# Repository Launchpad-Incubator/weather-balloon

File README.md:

# Weather Balloon Research

This is the research repository for the Launchpad weather balloon project. Add any useful information in the [wiki](https://github.com/Launchpad-Incubator/weather-balloon/wiki) under the appropriate page.

## Project Links

N/A (for now - **put OnShape link here**!)

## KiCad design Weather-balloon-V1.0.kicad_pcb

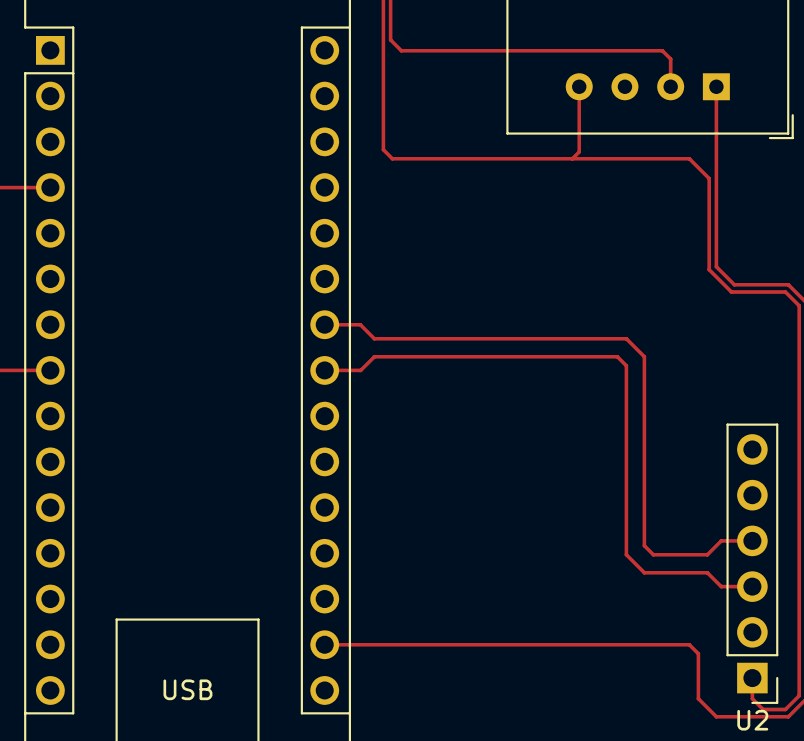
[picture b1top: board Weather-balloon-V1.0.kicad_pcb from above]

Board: 2 copper layers, 3 parts (0 on the bottom side), 5 nets.

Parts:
A1: Arduino_Nano_ESP32; Arduino_Nano
U1: AM2302; ASAIR_AM2302_P2.54mm_Vertical
U2: BMP280; PinHeader_1x06_P2.54mm_Vertical

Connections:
unnamed: A1.17 (3V3), U1.1 (VDD)
unnamed: A1.8 (D5), U1.2 (SDA)
unnamed: A1.4 (GND), A1.29 (GND), U1.3 (GND), U1.4 (GND), U2.1 (GND)
unnamed: A1.24 (SCL/A5), U2.4 (SCK)
unnamed: A1.23 (SDA/A4), U2.3 (SDI)

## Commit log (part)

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2025-10-22 Revise README for weather balloon project
    Updated project title and added description and links section.
2025-10-26 Update README with wiki link
2025-10-26 Add Project Links section to README
    Added a section for project links in the README.
2025-10-26 Add GitHub Actions for issue management automation
2025-10-26 Refactor issue management workflow conditions
2025-10-26 Add label-commenter configuration for duplicates
2025-10-26 Add permissions for issues in workflow
2025-10-26 Update README to highlight OnShape link placement
2025-10-26 Update project URL in GitHub Actions workflow
2025-10-29 Add contributing section to README
2025-11-08 Move README to .github directory
2025-11-09 Add Skew-T plot image
2025-11-09 Rename Screenshot 2025-10-26 155839.png to images/Skew-T_plot.png
2025-11-29 Add Spot Trace weight to component_weights.md
2026-01-22 Add Arduino Weather Station code
    Initial implementation of Arduino Weather Station code that reads temperature, humidity, and pressure from sensors and displays the data on a Nokia LCD.
2026-01-22 add correct file extension
2026-01-22 make compatible w/ Arduino Nano ESP32
2026-01-29 remove bmp085 calibration variables
2026-01-29 fix inverted logic D:
2026-01-29 cleaning up read sensors function and adding better logic :)
2026-01-29 fix the logic, fix dual variable assignment, and fix the structure being in inverse order
2026-01-29 add emoticons because i was bored and had nothing to do ¯\_(ツ)_/¯
2026-01-29 Rename code.ino to Code/archivedCode/code.ino
2026-01-29 Rename Code(BMP280Version).ino to main.ino
2026-02-05 Add enum, make cleaner logic, and QOL upd
2026-02-08 rename Images to Resources
2026-02-08 list the pins in the resources folder
2026-02-08 Update pinsForWiring
2026-02-08 <----- the pins for wiring are in here
2026-02-08 <----- code is in here
2026-02-12 <- Code w/ gps module
    Also has bmp 280 functionality & more
2026-02-12 fixed the gps thingy :D
2026-02-12 added the BMP280 without gps version here
2026-02-19 fix code
2026-02-19 Add APRS Notes for balloon tracking
    Added detailed notes for APRS balloon tracking including header format and data interpretation.
2026-02-19 <-- wiring here
2026-02-19 Revise timestamp format and add new APRS data
    Updated APRS Notes with corrected timestamp format and additional data.
2026-02-19 <-- things for payload that are important
2026-02-25 The code is in weather-balloon/Code/archivedCode/mainCode.ino
2026-02-26 <-- code here
2026-03-04 full code for now
2026-03-12 Update APRS Notes
2026-03-20 _____
2026-04-01 bugfixes
    1.) Code scope errors fixed
    2.) Infinite WIFI connect loop fixed
    3.) Optimizations
    4.) GPS failsafe improved
2026-04-01 bugfixes ++
    1.) Code scope errors fixed
    2.) Infinite WIFI connect loop fixed
    3.) Optimizations
    4.) GPS failsafe improved
2026-04-02 moar bugfixes
    and software serial is no more, now hardware serial
2026-04-06 MAJOR CHANGES!!!
    1.) More than one WIFI Network can be tried (so there's backups)
    2.) All data is formatted correctly now :>
    3.) Background WIFI retry is done on Core 0 (so it doesn't mess up timing or take processing power from the main code)
    4.) Much cleaner and some minor typos fixed
2026-04-06 Rename image.png to lol I asked Gemini for a graph representing some data and it gave me this.png
2026-04-06 beautiful
2026-04-06 amazinglicious
2026-05-07 yay, el gp del s
2026-05-27 Rename pinsForWiring to pinsForWiring.txt
2026-05-27 pins for wiring updated
2026-05-27 Rename pinsForWiring.md to pinsForWiring.txt
2026-05-28 annoying aidan with incorrect formatting
